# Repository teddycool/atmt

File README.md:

# atmt
A project to create an autonomous toy monster truck

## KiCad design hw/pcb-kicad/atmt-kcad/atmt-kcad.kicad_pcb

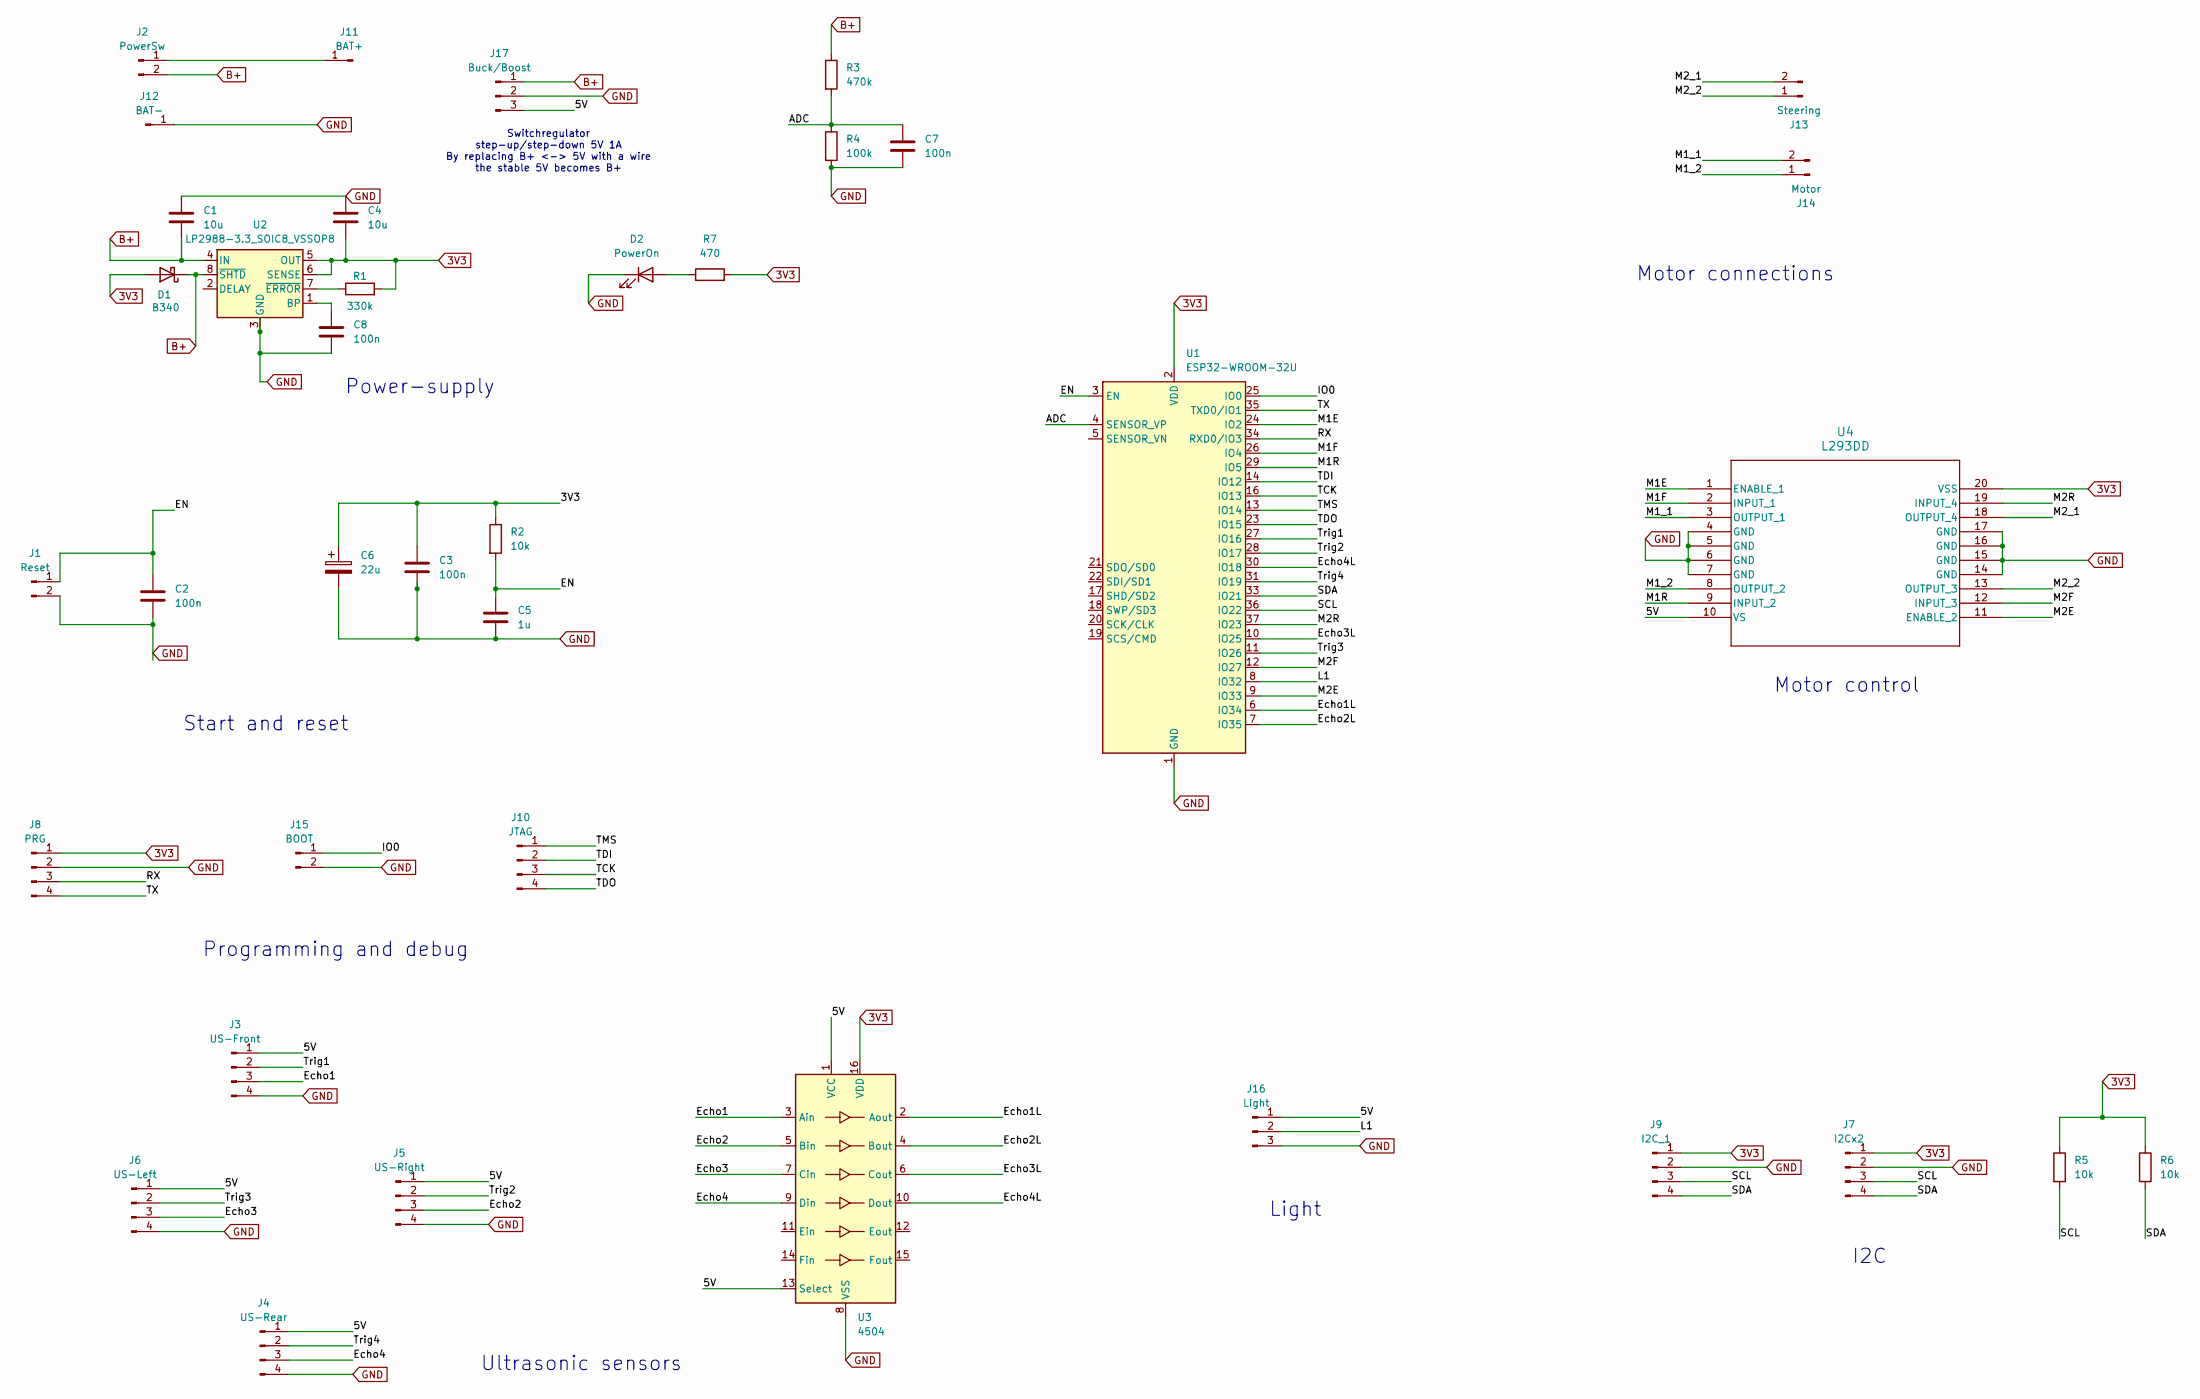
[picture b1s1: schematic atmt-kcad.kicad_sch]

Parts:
C1, C4: 10u; C_0805_2012Metric_Pad1.18x1.45mm_HandSolder
C2, C3, C7, C8: 100n; C_0805_2012Metric_Pad1.18x1.45mm_HandSolder
C5: 1u; C_0805_2012Metric_Pad1.18x1.45mm_HandSolder
C6: 22u; CP_Radial_D5.0mm_P2.00mm
D1: B340; D_SMC
D2: PowerOn; LED_D3.0mm
J1: Reset; PinHeader_1x02_P2.54mm_Vertical
J2: PowerSw; PinHeader_1x02_P2.54mm_Vertical
J3: US-Front; PinHeader_1x04_P2.54mm_Vertical
J4: US-Rear; PinHeader_1x04_P2.54mm_Vertical
J5: US-Right; PinHeader_1x04_P2.54mm_Vertical
J6: US-Left; PinHeader_1x04_P2.54mm_Vertical
J7: I2Cx2; PinHeader_1x04_P2.54mm_Vertical
J8: PRG; PinHeader_1x04_P2.54mm_Vertical
J9: I2C_1; PinHeader_1x04_P2.54mm_Vertical
J10: JTAG; PinHeader_1x04_P2.54mm_Vertical
J11: BAT+; SolderWire-1.5sqmm_1x01_D1.7mm_OD3mm
J12: BAT-; SolderWire-1.5sqmm_1x01_D1.7mm_OD3mm
J13: Steering; PhoenixContact_MSTBA_2,5_2-G-5,08_1x02_P5.08mm_Horizontal
J14: Motor; PhoenixContact_MSTBA_2,5_2-G-5,08_1x02_P5.08mm_Horizontal
J15: BOOT; PinHeader_1x02_P2.54mm_Vertical
J16: Light; PinHeader_1x03_P2.54mm_Vertical
J17: Buck/Boost; PinHeader_1x03_P2.54mm_Vertical
R1: 330k; R_0805_2012Metric_Pad1.20x1.40mm_HandSolder
R2, R5, R6: 10k; R_0805_2012Metric_Pad1.20x1.40mm_HandSolder
R3: 470k; R_0805_2012Metric_Pad1.20x1.40mm_HandSolder
R4: 100k; R_0805_2012Metric_Pad1.20x1.40mm_HandSolder
R7: 470; R_0805_2012Metric_Pad1.20x1.40mm_HandSolder
U1: ESP32-WROOM-32U
U2: LP2988-3.3_SOIC8_VSSOP8; SOIC-8_3.9x4.9mm_P1.27mm
U3: 4504; SOIC-16_3.9x9.9mm_P1.27mm
U4: L293DD; SO-20_STM

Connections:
3V3: C3.1, C4.2, C6.1, D1.2 (A), J7.1, J8.1, J9.1, R1.2, R2.1, R5.1, R6.1, R7.2, U1.2 (VDD), U2.5 (OUT), U2.6 (SENSE), U3.16 (VDD), U4.20 (VSS)
/5V: J3.1, J4.1, J5.1, J6.1, J16.1, J17.3, U3.1 (VCC), U3.13 (Select), U4.10 (VS)
/ADC: C7.1, R3.2, R4.1, U1.4 (SENSOR_VP)
/EN: C2.1, C5.1, J1.1, R2.2, U1.3 (EN)
/Echo1: J3.3, U3.3 (Ain)
/Echo1L: U1.6 (IO34), U3.2 (Aout)
/Echo2: J5.3, U3.5 (Bin)
/Echo2L: U1.7 (IO35), U3.4 (Bout)
/Echo3: J6.3, U3.7 (Cin)
/Echo3L: U1.10 (IO25), U3.6 (Cout)
/Echo4: J4.3, U3.9 (Din)
/Echo4L: U1.30 (IO18), U3.10 (Dout)
/IO0: J15.1, U1.25 (IO0)
/L1: J16.2, U1.8 (IO32)
/M1E: U1.24 (IO2), U4.1 (ENABLE_1)
/M1F: U1.26 (IO4), U4.2 (INPUT_1)
/M1R: U1.29 (IO5), U4.9 (INPUT_2)
/M1_1: J14.2, U4.3 (OUTPUT_1)
/M1_2: J14.1, U4.8 (OUTPUT_2)
/M2E: U1.9 (IO33), U4.11 (ENABLE_2)
/M2F: U1.12 (IO27), U4.12 (INPUT_3)
/M2R: U1.37 (IO23), U4.19 (INPUT_4)
/M2_1: J13.2, U4.18 (OUTPUT_4)
/M2_2: J13.1, U4.13 (OUTPUT_3)
/RX: J8.3, U1.34 (RXD0/IO3)
/SCL: J7.3, J9.3, R5.2, U1.36 (IO22)
/SDA: J7.4, J9.4, R6.2, U1.33 (IO21)
/TCK: J10.3, U1.16 (IO13)
/TDI: J10.2, U1.14 (IO12)
/TDO: J10.4, U1.23 (IO15)
/TMS: J10.1, U1.13 (IO14)
/TX: J8.4, U1.35 (TXD0/IO1)
/Trig1: J3.2, U1.27 (IO16)
/Trig2: J5.2, U1.28 (IO17)
/Trig3: J6.2, U1.11 (IO26)
/Trig4: J4.2, U1.31 (IO19)
B+: C1.2, D1.1 (K), J2.2, J17.1, R3.1, U2.4 (IN), U2.8 (~SHTD)
GND: C1.1, C2.2, C3.2, C4.1, C5.2, C6.2, C7.2, C8.2, D2.1 (K), J1.2, J3.4, J4.4, J5.4, J6.4, J7.2, J8.2, J9.2, J12.1, J15.2, J16.3, J17.2, R4.2, U1.1 (GND), U1.15 (GND), U1.38 (GND), U1.39 (GND), U2.3 (GND), U3.8 (VSS), U4.4 (GND), U4.5 (GND), U4.6 (GND), U4.7 (GND), U4.14 (GND), U4.15 (GND), U4.16 (GND), U4.17 (GND)
unnamed: D2.2 (A), R7.1
unnamed: J2.1, J11.1
unnamed: C8.1, U2.1 (BP)
unnamed: R1.1, U2.7 (~ERROR)

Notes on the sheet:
Motor control
Switchregulator step-up/step-down 5V 1A By replacing B+ <-> 5V with a wire the stable 5V becomes B+
Programming and debug
Motor connections
Light
I2C
Start and reset
Power-supply
Ultrasonic sensors

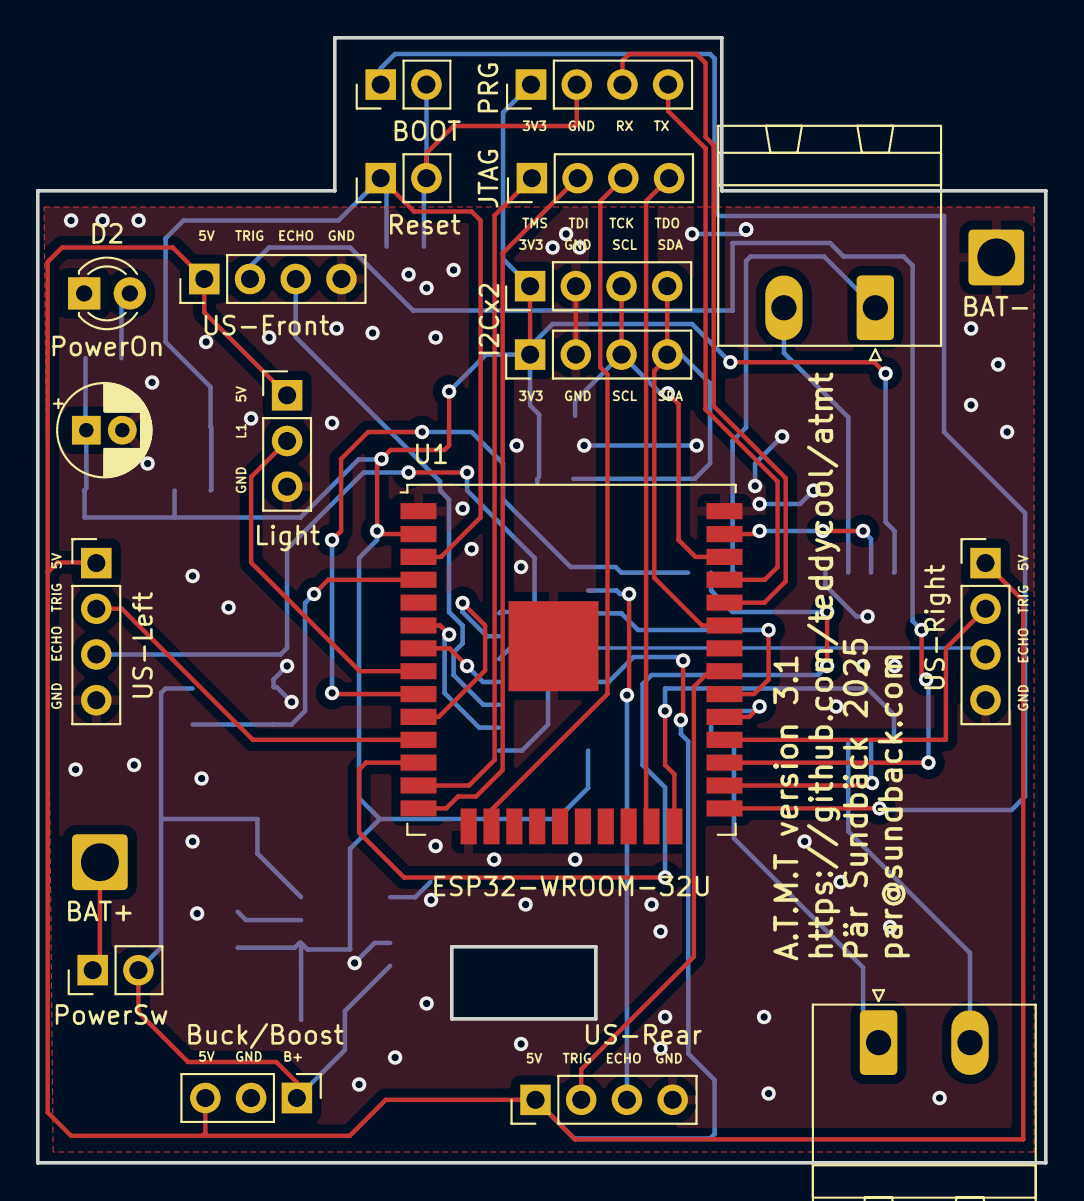
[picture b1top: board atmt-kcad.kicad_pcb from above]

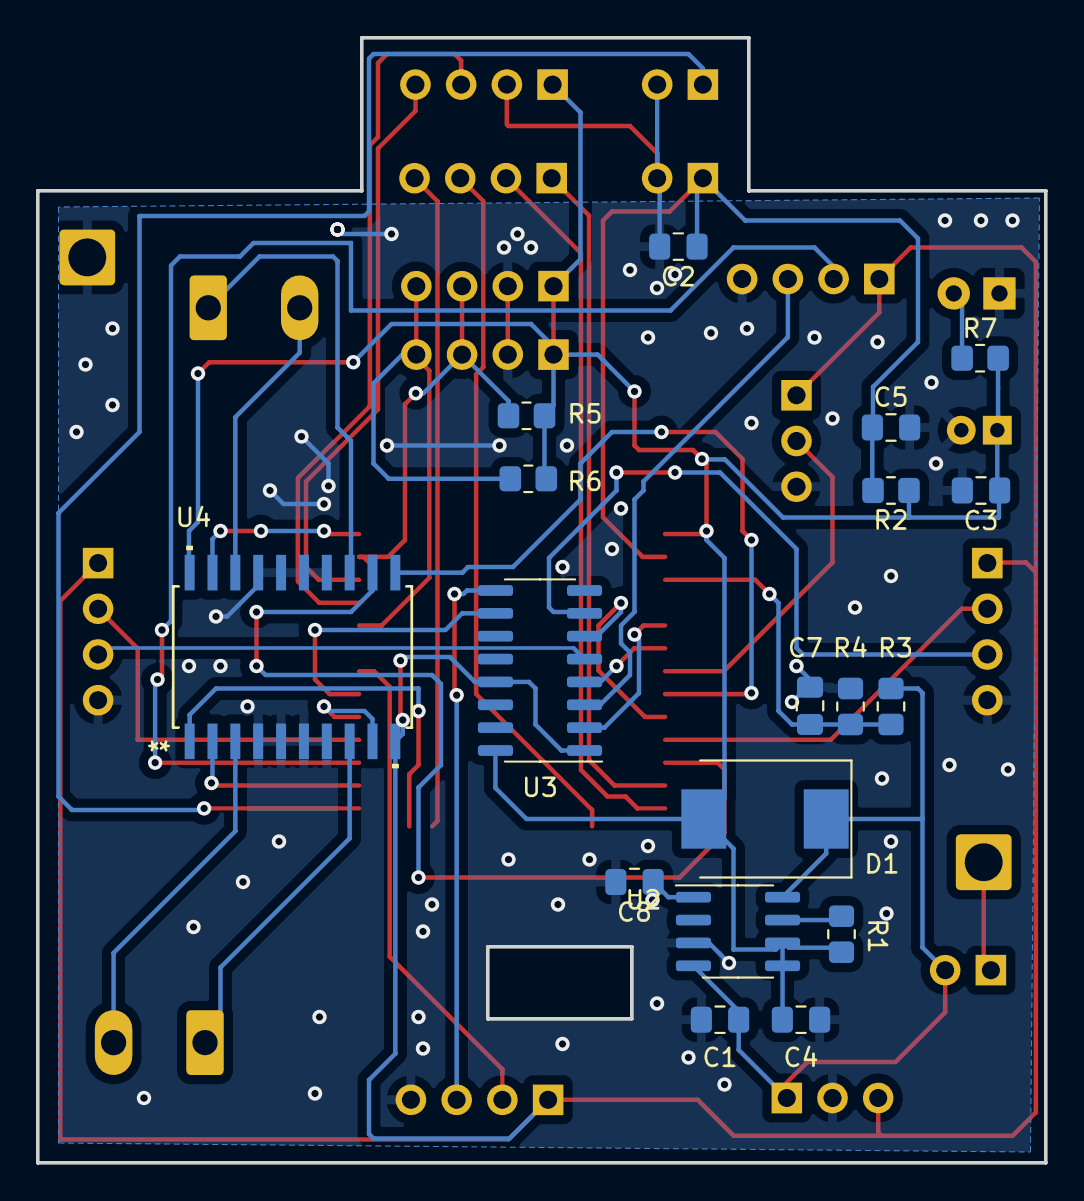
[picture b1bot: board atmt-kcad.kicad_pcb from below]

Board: 2 copper layers, 56.0 x 62.5 mm, 38 parts (18 on the bottom side), 42 nets.

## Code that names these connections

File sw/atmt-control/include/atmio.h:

#ifndef ATMIO_H
#define ATMIO_H  



// Define pin-name and GPIO#. Pin # are depending on HW version
// Naming is FIXED

//Hardware version 2:
//-------------------

// Motor
#define M1E_PIN 2
#define M1F_PIN 4
#define M1R_PIN 5

// Steering
#define SENABLE 33
#define SRIGHT 27
#define SLEFT 23

// US sensors
#define TFRONT 16 // ECHO1
#define EFRONT 34
#define TLEFT 26 // ECHO3
#define ELEFT 25
#define TREAR 19 // ECHO4
#define EREAR 18
#define TRIGHT 17 // ECHO2
#define ERIGHT 35


#endif

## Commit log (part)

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2021-02-07 First filedrop
2021-02-07 added readme
2021-02-20 first commit of control-sysetm
2021-03-25 new board
2021-04-16 new pcb
2022-11-05 Updated after MiniHack
2024-04-13 First step for scaniahack
2024-04-28 Major update and clean-up
2024-05-04 Update and restructured...
2024-05-05 two tasks working
2024-05-05 typ fungerande version, dock men lite hårdkodat.... Var problem hitta rtos headerfiler så fick lägga till -I i platform.io
2024-05-05 Adapted to the toy truck for left and right sensor,
2024-05-05 stopped tracking many files
2024-05-08 Deleted old directories and files
2024-05-08 Logging and db-setup
2024-05-10 Now there should ONLY be my readme file (#3)
    * working version with flashing of leds from two tasks
    * two tasks working
    * typ fungerande version, dock men lite hårdkodat.... Var problem hitta rtos headerfiler så fick lägga till -I i platform.io
    * ok
    * ok test of pralell data from ultrasound
    * Adapted to the toy truck for left and right sensor,
2024-05-10 Testocode that includes safe read/write
2024-05-10 Added compass to dynamics and log to backend for all values
2024-05-12 Added a index.php file with a hellow world code and view_logs.php with the logic to visualize the logs
2024-05-13 Working example version for the truck, magnetic sensor part not testing as I do not have one
2024-05-13 Added a index.php file with a hellow world code and view_logs.php with the logic to visualize the logs (#7)
2024-05-16 Reversed order of logs to show latest on top
2024-05-16 Updated the index.php file from the rpi to the repo and added links from home to view logs and vise versa
2024-05-16 added a link to ota
2024-05-16 test
2024-05-16 strategy
2024-05-16 reverse back and forward
2024-05-16 strategy forward, backward, lights
2024-05-16 Statisc ip
2024-05-16 reverse when close
2024-05-16 reverse if something ahead
2024-05-16 forward if something behind
2024-05-16 ipadresser
2024-05-16 added mqtt measurement
2024-05-16 ip adresser take 3
2024-05-16 master strat
2024-05-16 Vehicle goes ztright based on gyro feedback (#11)
    * working version with flashing of leds from two tasks
    * two tasks working
    * typ fungerande version, dock men lite hårdkodat.... Var problem hitta rtos headerfiler så fick lägga till -I i platform.io
    * ok
    * ok test of pralell data from ultrasound
    * Adapted to the toy truck for left and right sensor,
2024-05-16 mqtt measurements shorter variable names
2024-05-16 added arduino json lib
2024-05-16 before nerge
2024-05-17 Get Mqtt messages but does loose many
2024-05-17 Removed postvalue function
2024-05-17 added agian iteration++ counter in the loop function
2024-05-17 cleaned some lines of code
2024-05-17 friday morning
2024-05-17 integrated sensor services
2024-05-17 changed delay(ms) function to Delay(vTaskDelay(pdMS_TO_TICKS(ms)))
2024-05-17 Added simple strategy without sensors
2024-05-17 not working
2024-05-17 invert steering when reverse
2024-05-17 Check if object on both sides
2024-05-28 Start of clean-up and restructure
2024-07-05 Before new branch
2025-01-31 First restruct
2025-01-31 Created a random foo file
2025-01-31 Scacaniahack 2024
2025-02-01 Updated docs
2025-02-01 AI generated example (not yet tested) as how to create different types of tasks.
2025-02-01 corrected the include paths
2025-02-01 Updated secrets and atmio definitions
2025-02-01 Examples directory started. (#22)
    * Scacaniahack 2024
    * AI generated example (not yet tested) as how to create different types of tasks.
    * corrected the include paths
    * calssing started. realised it will be very difficult to keep interrupts separate and to avoid the sensors disturb each other. So a redesign wioll be needed. COnstructor to create a table, then you 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
    ---------
2025-02-02 Restructure and new hw-test-sw
2025-02-07 Backup commit
2025-02-07 Usensor (#23)
    * Scacaniahack 2024
    * AI generated example (not yet tested) as how to create different types of tasks.
    * corrected the include paths
    * calssing started. realised it will be very difficult to keep interrupts separate and to avoid the sensors disturb each other. So a redesign wioll be needed. COnstructor to create a table, then you 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
    * Passing compilation for z_main_usensor for the first time. Linking problem, and not yet tested
    * Backup commit
2025-02-08 New kicad and a new hello-world-sw
2025-02-08 Seems to be working, Back sensor gives correct numbers, the other not, but could be cable problems (#24)
2025-02-08 First working new motor control. Only drive is implem,ented, breaking can be done later. Expect to use quite high number: 80-100 % for enough torque at 4-5 v.
2025-02-08 Removed a couple of defines that were not used.
2025-02-08 Docementation on how to build separate tests in platformio. First version.
2025-02-08 First working motor control with test pack that runs motor forward and backwards (#25)
    * Seems to be working, Back sensor gives correct numbers, the other not, but could be cable problems
    * First working new motor control. Only drive is implem,ented, breaking can be done later. Expect to use quite high number: 80-100 % for enough torque at 4-5 v.
    * Removed a couple of defines that were not used.
    * Docementation on how to build separate tests in platformio. First version.
    ---------
2025-02-08 First structure for the config package
2025-02-10 Unsensor (#26)
    * Seems to be working, Back sensor gives correct numbers, the other not, but could be cable problems
    * First working new motor control. Only drive is implem,ented, breaking can be done later. Expect to use quite high number: 80-100 % for enough torque at 4-5 v.
    * Removed a couple of defines that were not used.
    * Docementation on how to build separate tests in platformio. First version.
    * First structure for the config package
    * Higly improved Usensor, both the component test that shows both distance and age. And the comments and structure in the usensor class has been improved, especially around the POLL_INTERVAL
2025-02-10 Updated documents
2025-02-16 Logger and test_main
2025-02-16 Cleaned up and restructured a bit, preparing for different chassi-typesusing the same electronics
2025-02-22 New structure but still working as before
2025-02-23 MQTT step 1 and a telemetry-module
2025-03-01 Updated and tested usensor in accordance with the new directory structure
2025-03-01 updated platformio.ini (#27)
    * updated platformio.ini
    * Updated and tested usensor in accordance with the new directory structure
    ---------
2025-03-01 Added accsensor and all uodates required for that. It could be that the change of setget to long instead of int coaul case some issues with other packets, needs to be verified. maybe overlaying so th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
2025-03-01 Seems I missed these two for my accsensor commit.
2025-03-06 More to pull (#29)
    * updated platformio.ini
    * Updated and tested usensor in accordance with the new directory structure
    * Added accsensor and all uodates required for that. It could be that the change of setget to long instead of int coaul case some issues with other packets, needs to be verified. maybe overlaying so 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
    * Seems I missed these two for my accsensor commit.
    ---------
2025-03-08 First shot of kalman-filter for acc
2025-03-08 docs update
2025-03-08 First shot compass
2025-03-09 Fixed plattform.ini
2025-03-09 Accsensorcalibration added
2025-03-09 New steer, which lead to other modifications and improvements.... (#30)
    * Mainly recreation of steer, but some other updates were also required.
    * Accsensorcalibration added
    ---------
2025-03-09 z_main_steer_test file which initiates the setget before it is used by steer.
2025-03-09 Corrected the PWM channel since the motor package need booth ch0 and ch 1 when using differential steering.
2025-03-09 added so that both proportional sterring as well as the original digital steering is tested.
2025-03-10 Uppdates ragerding steering, should now support ordinary motor and not only servo (#31)
    * Updated needed files to support so that steer.direction stores the latest steering number in the globalVar steerDirection. This is so that motor:drive can read and use this information if different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
    * z_main_steer_test file which initiates the setget before it is used by steer.
    * Corrected the PWM channel since the motor package need booth ch0 and ch 1 when using differential steering.
    * Added support for the normal motor instead of a servo for steering.
    * added so that both proportional sterring as well as the original digital steering is tested
2025-03-10 old header files in old location. Needs to be removed to avoid confusion
2025-03-11 added missing ref to config.cpp for env:motor
2025-03-15 Hardware test program
2025-03-17 gy271
2025-03-17 expander working basic
2025-03-17 differential basic support added to motor
2025-03-17 simple i2c scanner to find unknown addresses
2025-03-18 Some updates
2025-03-18 merging into main
2025-03-18 merged from upstream with my code
2025-03-18 corrected default config to be SINGLE motor and MOTOR steering.
2025-03-18 Localdev
2025-03-18 Minor fixes to get motor and steer to build agan. Had to remove strange lib dependency I dfo not have and packages do not need. In steer the use of the calculated variables and the correct calls to l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
2025-03-20 Added ESP32 ID of JCA01 to config file
2025-03-20 Remove .vscode directory from Git tracking
2025-03-20 Sensor-values in structure, motor stops when clesd to obstacle
2025-03-20 remove vscode
2025-03-20 Simple bash remote control client via mqtt.
2025-03-20 Now with minimum delay in MQTT messaging
2025-03-20 Added remote bash client with new jeson format with 10 degrees precision for steering
2025-03-20 Added yolo script for video detection
2025-03-21 Changed the detection script to detect only cup, bottle, toothbrush, apple and cellphone
2025-03-21 added detection for moving forward and stop using yolo
2025-03-21 Remote-controls
2025-03-21 added requirements and README.md file to bash_remote_control
2025-03-21 moved remote.sh script and detection_script.py to remote directory
2025-03-22 motor reworked as well as config and setget. All to make packages more consistant, remove the unpredictable class instantiations and instead use regular function calls.
2025-03-23 Added options to remote.sh to be able to choose VEHICLE_ID and MQTT broker as arguments to the command line. Added a Usage description. If no option is given, it runs with the default ones from the S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
2026-02-21 Status before scaniahack 2026
2026-02-21 Add comprehensive .gitignore for embedded development project
    - PlatformIO build artifacts and IDE files
    - Python virtual environments and bytecode
    - KiCad backup and temporary files
    - FreeCAD backup files
    - OS and IDE temporary files
    - Security-sensitive files (secrets.h, config files)
2026-03-16 Before cleanup for ScaniaHack-2026
2026-03-16 Removed unused code and files
2026-03-16 Rename: sw -> EmbeddedSw - Update VS Code configs and documentation
2026-03-16 Huge restructure forScaniaHack 2026
2026-03-19 Before
2026-03-19 Added config
2026-03-19 added truck simulator and added gitignore for avoid adding venv to git
2026-03-19 refactored the code to have a more modular way of putting an explore strategy
2026-03-19 changed the truck simulation code to start at a random place and to send the data every second.
2026-03-19 Changed the view of the map visualizer to plot every sensor separately
2026-03-19 Fixed crack/reboot and motorparameters
2026-03-19 Visualization of the truck_simulator is working good, but not the strategy
2026-03-19 Added embedded control that simulated the explore logic in the embedded system. It is working well.
2026-03-19 added json structure into the guardrails
2026-03-19 added drift to the streight drive in the truck simulator, added rdp to get the final map to the map visualizator
2026-03-19 changed to L shape for the simulator
2026-03-19 New json
2026-03-20 added a new simulator and room mapper, also added a truck_remote script that implements different exploration strategies
2026-03-20 changed the direction stength to 60 in remote
